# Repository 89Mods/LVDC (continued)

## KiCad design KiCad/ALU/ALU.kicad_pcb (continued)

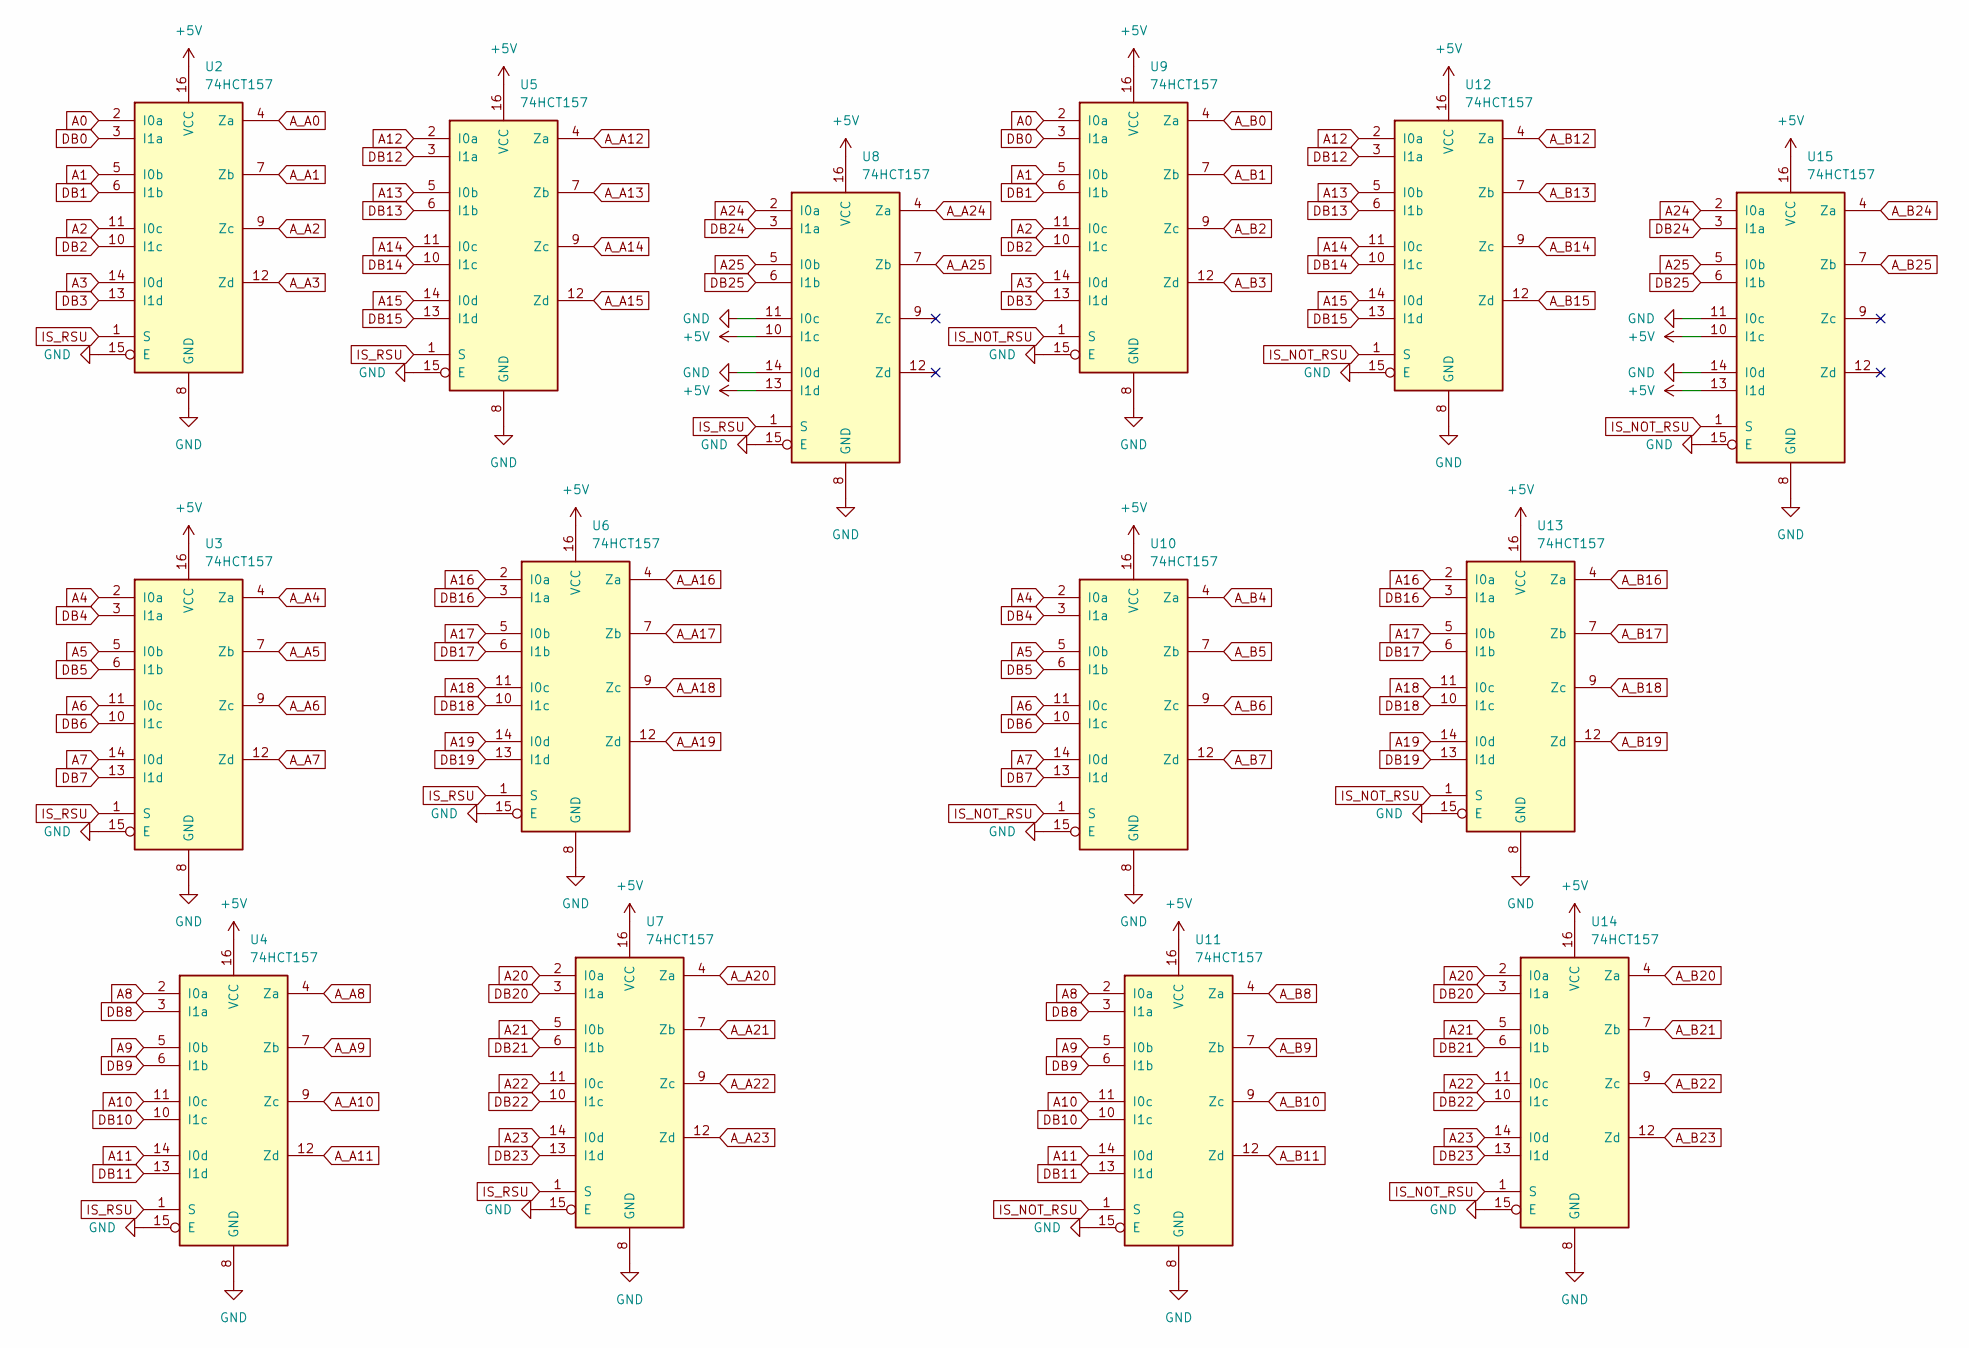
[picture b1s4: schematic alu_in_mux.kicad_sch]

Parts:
U2, U3, U4, U5, U6, U7, U8, U9, U10, U11, U12, U13, U14, U15: 74HCT157; SO-16_3.9x9.9mm_P1.27mm

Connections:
+5V: U2.16 (VCC), U3.16 (VCC), U4.16 (VCC), U5.16 (VCC), U6.16 (VCC), U7.16 (VCC), U8.10 (I1c), U8.13 (I1d), U8.16 (VCC), U9.16 (VCC), U10.16 (VCC), U11.16 (VCC), U12.16 (VCC), U13.16 (VCC), U14.16 (VCC), U15.10 (I1c), U15.13 (I1d), U15.16 (VCC); also elsewhere on the board
A0: U2.2 (I0a), U9.2 (I0a); also elsewhere on the board
A1: U2.5 (I0b), U9.5 (I0b); also elsewhere on the board
A2: U2.11 (I0c), U9.11 (I0c); also elsewhere on the board
A3: U2.14 (I0d), U9.14 (I0d); also elsewhere on the board
A4: U3.2 (I0a), U10.2 (I0a); also elsewhere on the board
A5: U3.5 (I0b), U10.5 (I0b); also elsewhere on the board
A6: U3.11 (I0c), U10.11 (I0c); also elsewhere on the board
A7: U3.14 (I0d), U10.14 (I0d); also elsewhere on the board
A8: U4.2 (I0a), U11.2 (I0a); also elsewhere on the board
A9: U4.5 (I0b), U11.5 (I0b); also elsewhere on the board
A10: U4.11 (I0c), U11.11 (I0c); also elsewhere on the board
A11: U4.14 (I0d), U11.14 (I0d); also elsewhere on the board
A12: U5.2 (I0a), U12.2 (I0a); also elsewhere on the board
A13: U5.5 (I0b), U12.5 (I0b); also elsewhere on the board
A14: U5.11 (I0c), U12.11 (I0c); also elsewhere on the board
A15: U5.14 (I0d), U12.14 (I0d); also elsewhere on the board
A16: U6.2 (I0a), U13.2 (I0a); also elsewhere on the board
A17: U6.5 (I0b), U13.5 (I0b); also elsewhere on the board
A18: U6.11 (I0c), U13.11 (I0c); also elsewhere on the board
A19: U6.14 (I0d), U13.14 (I0d); also elsewhere on the board
A20: U7.2 (I0a), U14.2 (I0a); also elsewhere on the board
A21: U7.5 (I0b), U14.5 (I0b); also elsewhere on the board
A22: U7.11 (I0c), U14.11 (I0c); also elsewhere on the board
A23: U7.14 (I0d), U14.14 (I0d); also elsewhere on the board
A24: U8.2 (I0a), U15.2 (I0a); also elsewhere on the board
A25: U8.5 (I0b), U15.5 (I0b); also elsewhere on the board
A_A0: U2.4 (Za); also elsewhere on the board
A_A1: U2.7 (Zb); also elsewhere on the board
A_A2: U2.9 (Zc); also elsewhere on the board
A_A3: U2.12 (Zd); also elsewhere on the board
A_A4: U3.4 (Za); also elsewhere on the board
A_A5: U3.7 (Zb); also elsewhere on the board
A_A6: U3.9 (Zc); also elsewhere on the board
A_A7: U3.12 (Zd); also elsewhere on the board
A_A8: U4.4 (Za); also elsewhere on the board
A_A9: U4.7 (Zb); also elsewhere on the board
A_A10: U4.9 (Zc); also elsewhere on the board
A_A11: U4.12 (Zd); also elsewhere on the board
A_A12: U5.4 (Za); also elsewhere on the board
A_A13: U5.7 (Zb); also elsewhere on the board
A_A14: U5.9 (Zc); also elsewhere on the board
A_A15: U5.12 (Zd); also elsewhere on the board
A_A16: U6.4 (Za); also elsewhere on the board
A_A17: U6.7 (Zb); also elsewhere on the board
A_A18: U6.9 (Zc); also elsewhere on the board
A_A19: U6.12 (Zd); also elsewhere on the board
A_A20: U7.4 (Za); also elsewhere on the board
A_A21: U7.7 (Zb); also elsewhere on the board
A_A22: U7.9 (Zc); also elsewhere on the board
A_A23: U7.12 (Zd); also elsewhere on the board
A_A24: U8.4 (Za); also elsewhere on the board
A_A25: U8.7 (Zb); also elsewhere on the board
A_B0: U9.4 (Za); also elsewhere on the board
A_B1: U9.7 (Zb); also elsewhere on the board
A_B2: U9.9 (Zc); also elsewhere on the board
A_B3: U9.12 (Zd); also elsewhere on the board
A_B4: U10.4 (Za); also elsewhere on the board
A_B5: U10.7 (Zb); also elsewhere on the board
A_B6: U10.9 (Zc); also elsewhere on the board
A_B7: U10.12 (Zd); also elsewhere on the board
A_B8: U11.4 (Za); also elsewhere on the board
A_B9: U11.7 (Zb); also elsewhere on the board
A_B10: U11.9 (Zc); also elsewhere on the board
A_B11: U11.12 (Zd); also elsewhere on the board
A_B12: U12.4 (Za); also elsewhere on the board
A_B13: U12.7 (Zb); also elsewhere on the board
A_B14: U12.9 (Zc); also elsewhere on the board
A_B15: U12.12 (Zd); also elsewhere on the board
A_B16: U13.4 (Za); also elsewhere on the board
A_B17: U13.7 (Zb); also elsewhere on the board
A_B18: U13.9 (Zc); also elsewhere on the board
A_B19: U13.12 (Zd); also elsewhere on the board
A_B20: U14.4 (Za); also elsewhere on the board
A_B21: U14.7 (Zb); also elsewhere on the board
A_B22: U14.9 (Zc); also elsewhere on the board
A_B23: U14.12 (Zd); also elsewhere on the board
A_B24: U15.4 (Za); also elsewhere on the board
A_B25: U15.7 (Zb); also elsewhere on the board
DB0: U2.3 (I1a), U9.3 (I1a); also elsewhere on the board
DB1: U2.6 (I1b), U9.6 (I1b); also elsewhere on the board
DB2: U2.10 (I1c), U9.10 (I1c); also elsewhere on the board
DB3: U2.13 (I1d), U9.13 (I1d); also elsewhere on the board
DB4: U3.3 (I1a), U10.3 (I1a); also elsewhere on the board
DB5: U3.6 (I1b), U10.6 (I1b); also elsewhere on the board
DB6: U3.10 (I1c), U10.10 (I1c); also elsewhere on the board
DB7: U3.13 (I1d), U10.13 (I1d); also elsewhere on the board
DB8: U4.3 (I1a), U11.3 (I1a); also elsewhere on the board
DB9: U4.6 (I1b), U11.6 (I1b); also elsewhere on the board
DB10: U4.10 (I1c), U11.10 (I1c); also elsewhere on the board
DB11: U4.13 (I1d), U11.13 (I1d); also elsewhere on the board
DB12: U5.3 (I1a), U12.3 (I1a); also elsewhere on the board
DB13: U5.6 (I1b), U12.6 (I1b); also elsewhere on the board
DB14: U5.10 (I1c), U12.10 (I1c); also elsewhere on the board
DB15: U5.13 (I1d), U12.13 (I1d); also elsewhere on the board
DB16: U6.3 (I1a), U13.3 (I1a); also elsewhere on the board
DB17: U6.6 (I1b), U13.6 (I1b); also elsewhere on the board
DB18: U6.10 (I1c), U13.10 (I1c); also elsewhere on the board
DB19: U6.13 (I1d), U13.13 (I1d); also elsewhere on the board
DB20: U7.3 (I1a), U14.3 (I1a); also elsewhere on the board
DB21: U7.6 (I1b), U14.6 (I1b); also elsewhere on the board
DB22: U7.10 (I1c), U14.10 (I1c); also elsewhere on the board
DB23: U7.13 (I1d), U14.13 (I1d); also elsewhere on the board
DB24: U8.3 (I1a), U15.3 (I1a); also elsewhere on the board
DB25: U8.6 (I1b), U15.6 (I1b); also elsewhere on the board
GND: U2.8 (GND), U2.15 (E), U3.8 (GND), U3.15 (E), U4.8 (GND), U4.15 (E), U5.8 (GND), U5.15 (E), U6.8 (GND), U6.15 (E), U7.8 (GND), U7.15 (E), U8.8 (GND), U8.11 (I0c), U8.14 (I0d), U8.15 (E), U9.8 (GND), U9.15 (E), U10.8 (GND), U10.15 (E), U11.8 (GND), U11.15 (E), U12.8 (GND), U12.15 (E), U13.8 (GND), U13.15 (E), U14.8 (GND), U14.15 (E), U15.8 (GND), U15.11 (I0c), U15.14 (I0d), U15.15 (E); also elsewhere on the board
IS_NOT_RSU: U9.1 (S), U10.1 (S), U11.1 (S), U12.1 (S), U13.1 (S), U14.1 (S), U15.1 (S); also elsewhere on the board
IS_RSU: U2.1 (S), U3.1 (S), U4.1 (S), U5.1 (S), U6.1 (S), U7.1 (S), U8.1 (S); also elsewhere on the board

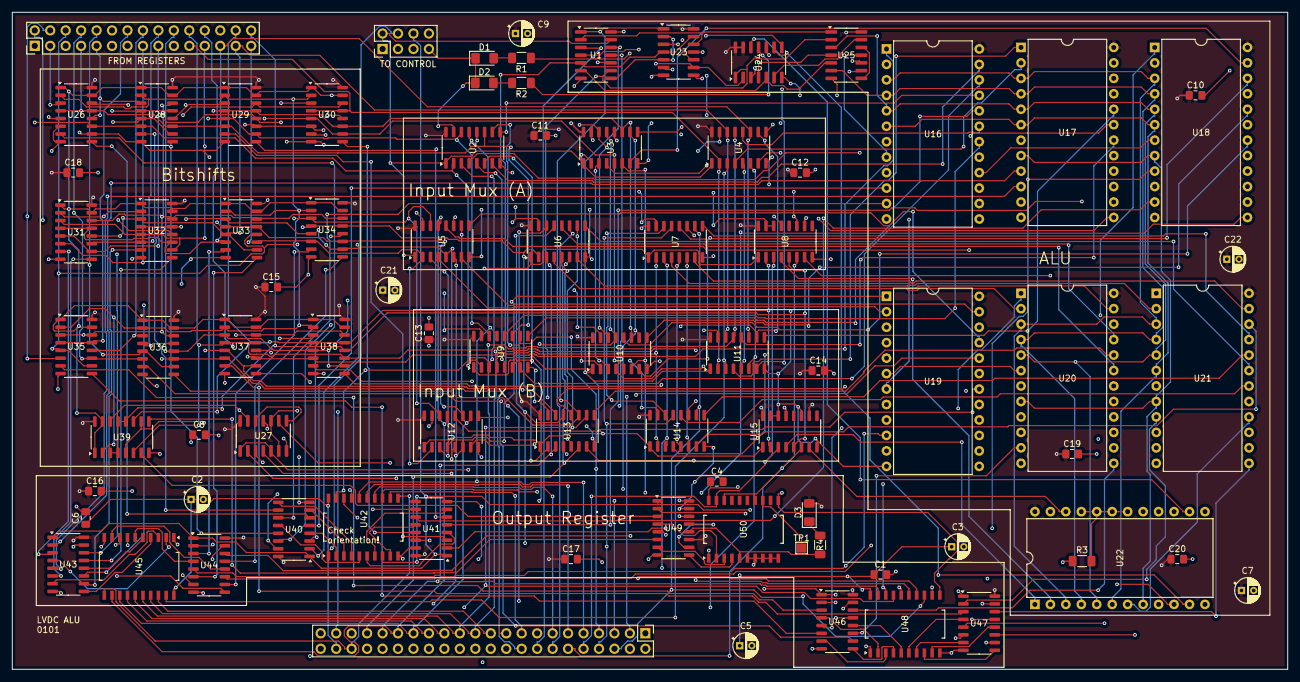
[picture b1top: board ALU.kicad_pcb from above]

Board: 4 copper layers, 209.5 x 108.0 mm, 83 parts (0 on the bottom side), 234 nets.

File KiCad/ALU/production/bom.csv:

Designator,Footprint,Quantity,Value,LCSC Part #
"C1, C10, C11, C12, C13, C14, C15, C16, C17, C18, C19, C20, C4, C6, C8",0805,15,100nF,
"C2, C21, C22, C3, C5, C7, C9",CP_Radial_D4.0mm_P2.00mm,7,10µF,
"D1, D2, D3",1206,3,LED,
J1,PinHeader_2x15_P2.54mm_Vertical,1,ACCUMULATOR,
J2,PinHeader_2x22_P2.54mm_Vertical,1,TO_BACKPLANE,
J3,PinHeader_2x04_P2.54mm_Vertical,1,FROM_CTRL,
"R1, R2, R3, R4",1206,4,1K,
TP1,TestPoint_Pad_1.5x1.5mm,1,TestPoint,
U1,SO-14_3.9x8.65mm_P1.27mm,1,74HCT04,
"U10, U11, U12, U13, U14, U15, U2, U3, U4, U40, U41, U43, U44, U46, U47, U49, U5, U6, U7, U8, U9",SO-16_3.9x9.9mm_P1.27mm,21,74HCT157,
"U16, U17, U18, U19, U20, U21, U22",DIP-24_W15.24mm,7,74LS181,
"U23, U24",SO-14_3.9x8.65mm_P1.27mm,2,74HCT08,
"U25, U27",SO-14_3.9x8.65mm_P1.27mm,2,74HCT32,
"U26, U28, U29, U30, U31, U32, U33, U34, U35, U36, U37, U38, U39",SO-16_3.9x9.9mm_P1.27mm,13,74HCT153,
"U42, U45, U48, U50",SO-20_12.8x7.5mm_P1.27mm,4,74HCT574,
